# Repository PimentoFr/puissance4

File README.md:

# puissance4
Il s'agit d'un puissance 4 lumineux connecté et interractif par le chat Twitch

# Description

Ce projet a pour but de réaliser un écran LED basé sur des WS2812B (led addressable individuellement), piloté par un raspberry pi
afin d'ouvrir une surface de jeu pour le puissance 4. Le jeu sera connecté et intéractif avec le chat Twitch pour permettre
aux viewers et participants de chat de jouer leur partie.

Dans ce projet, l'arborescence est la suivante:
- `hardware` : L'ensemble des documents permettant la réalisation des cartes électroniques du projet
    - `panneau_led`: Contient le design de la carte électronique des dalles de LEDs.
    - `mainboard`: Carte principale permettant l'alimentation des Bucks 24V-5V pour les colonnes de la matrice de LEDs et la connection
    du Raspberry Pi.
- `software` : Bientôt.

# Logiciels

Les logiciels utilisées sont les suivants:
- hardware : [Kicad](https://kicad.org/download/)

# Electronique

## Panneau led

Les panneaux LEDs sont des panneaux de 90x90mm qui accueille chacun 9 LEDs de type WS2812B.
Elles sont tous chaînés de la manière suivante:

```
1 -> 2 -> 3
 <--------|
4 -> 5 -> 6
 <--------|
7 -> 8 -> 9
```

## Mainboard

Cette carte permet d'accueillir la source d'alimentation (Prise Power Jack 24V 4A) et de la répartir sur 7 borniers afin d'y brancher 7 convertisseurs DC/DC Buck pour alimenter chacun des 7 colonnes de la matrice de LEDs.
A cela, un support femelle 2x20 pins permet de connnecter un
Raspberry Pi afin d'assurer l'intelligence et le pilotage de ce
panneau LEDs. Un level shifter 3.3V->5V permet d'assurer l'adaptation de niveau logique entre la commande émise par le
Raspberry Pi et les WS2812B.

Plusieurs connecteurs supplémentaires permettent de brancher
d'autres périphériques au besoin en I2C/SPI/UART.

# Licence

Le projet est open-source. Tout le monde peut l'utiliser en laissant la référence à son auteur.

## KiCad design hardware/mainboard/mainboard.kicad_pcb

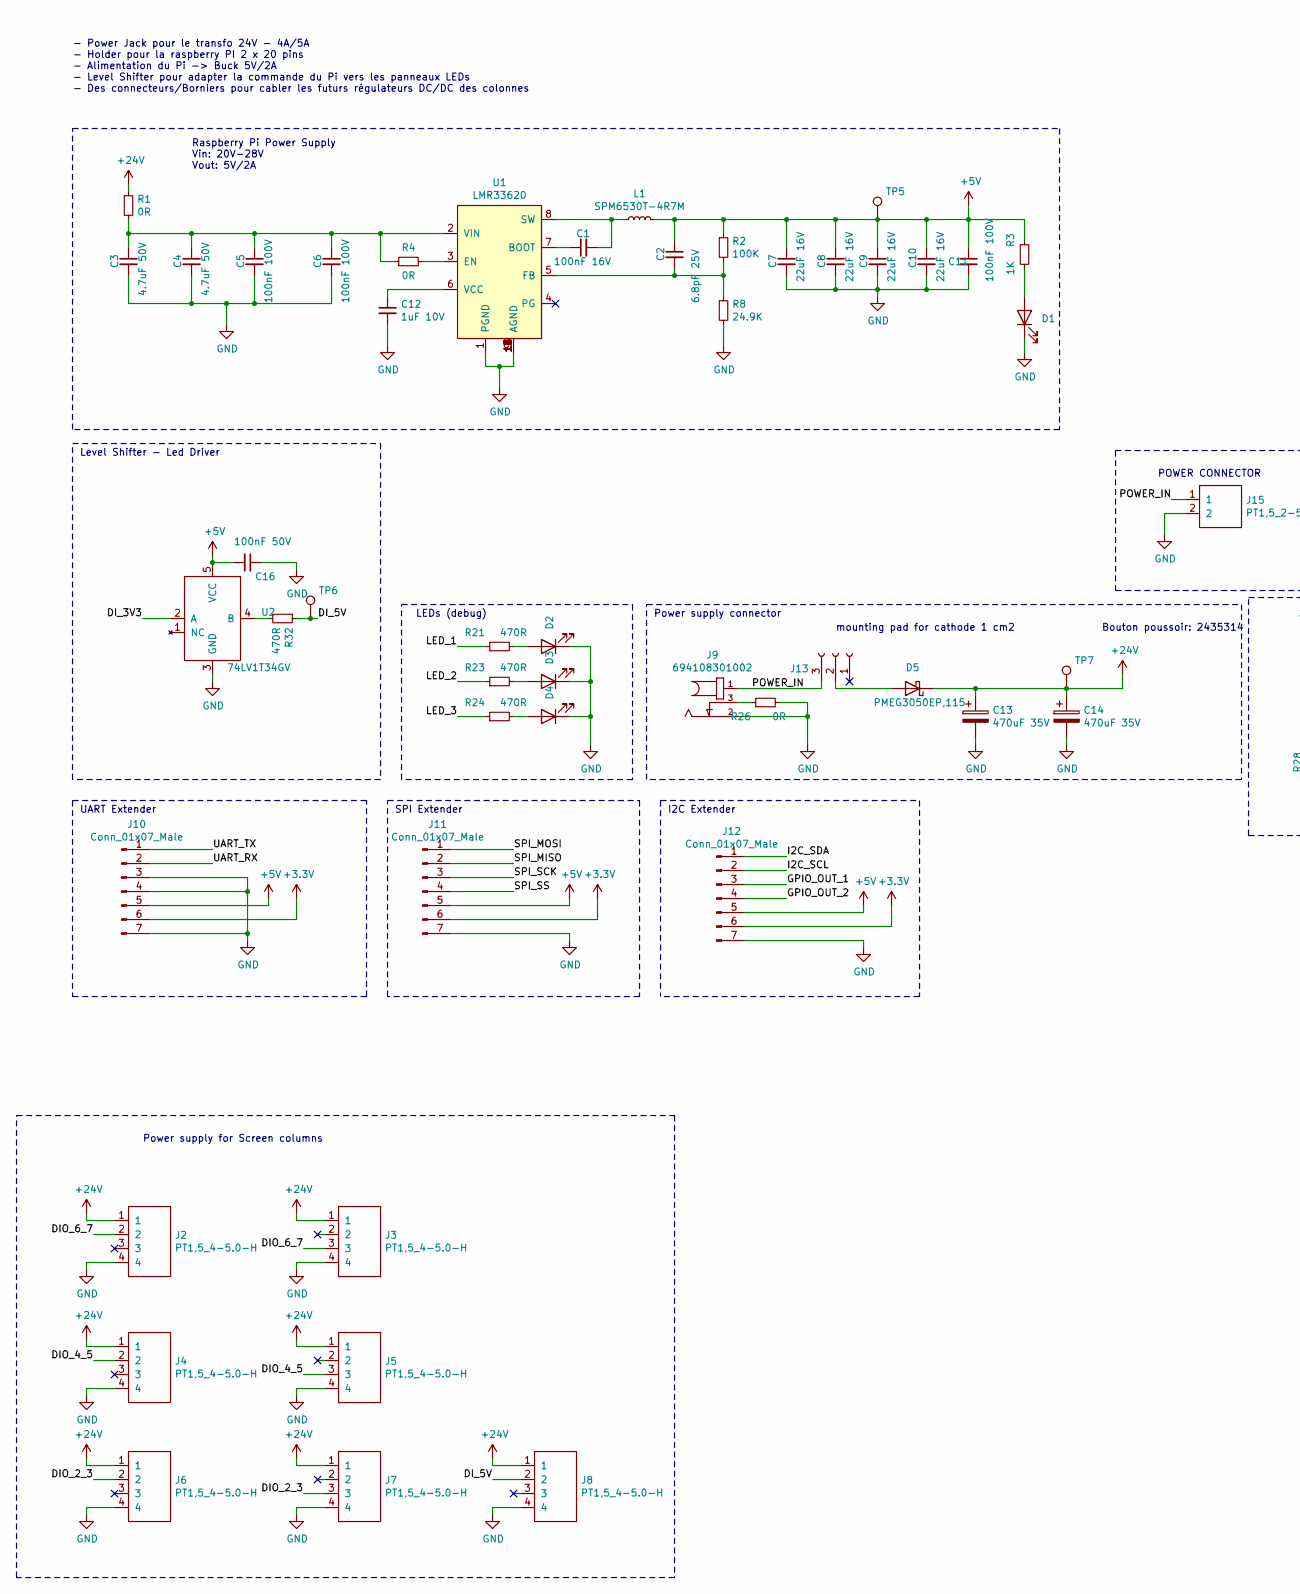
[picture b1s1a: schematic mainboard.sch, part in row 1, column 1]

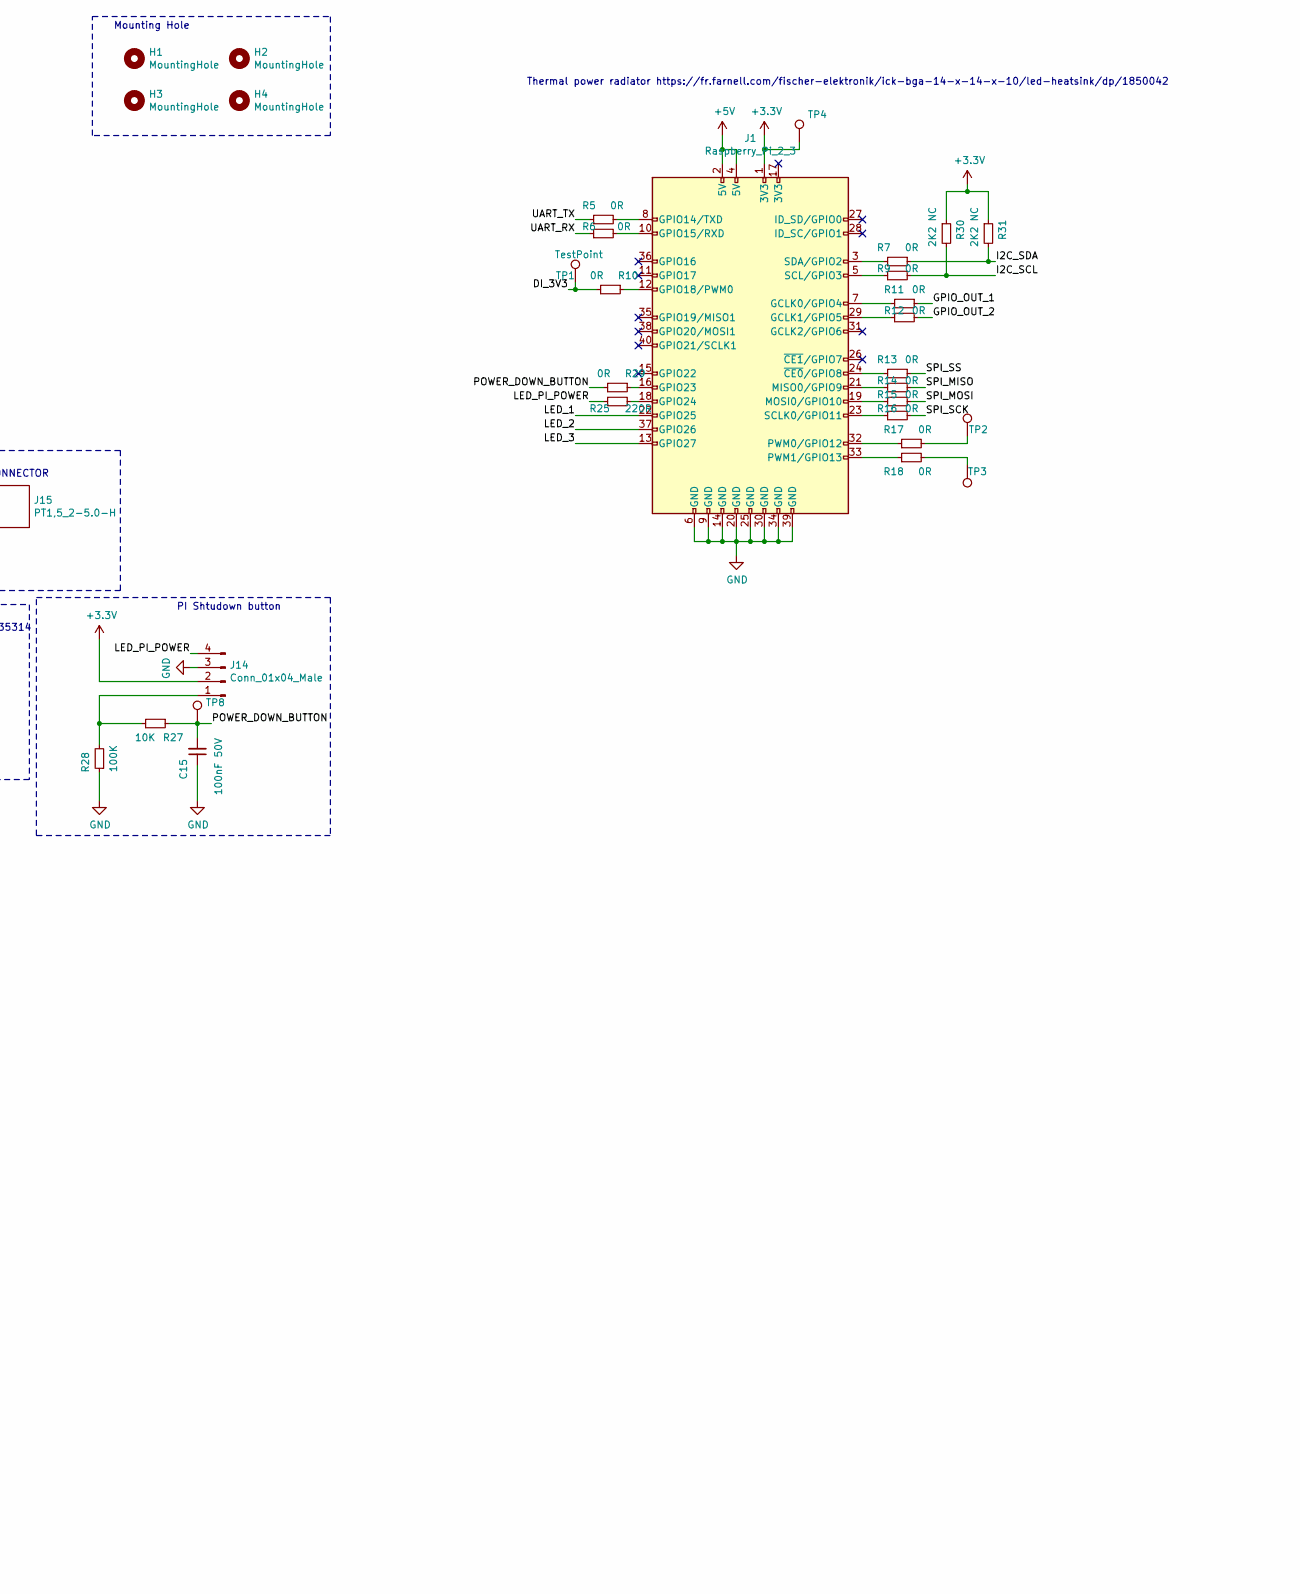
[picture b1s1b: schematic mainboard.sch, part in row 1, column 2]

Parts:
C1: 100nF 16V; C_0402_1005Metric; farnell 2627345
C2: 6.8pF 25V; C_0402_1005Metric; farnell 2781440
C3: 4.7uF 50V; C_1206_3216Metric_Pad1.42x1.75mm_HandSolder; farnell 1735545
C4: 4.7uF 50V; C_1206_3216Metric_Pad1.42x1.75mm_HandSolder
C5, C6, C11: 100nF 100V; C_0603_1608Metric_Pad1.05x0.95mm_HandSolder; farnell 1828921
C7, C8, C9, C10: 22uF 16V; C_1210_3225Metric_Pad1.42x2.65mm_HandSolder; farnell 2112725
C12: 1uF 10V; C_0603_1608Metric_Pad1.05x0.95mm_HandSolder; farnell 9227776
C13, C14: 470uF 35V; CP_Radial_D10.0mm_P5.00mm; farnell 2805546
C15, C16: 100nF 50V; C_0402_1005Metric
D1, D2, D3, D4: MCL-S250GC; LED_1206_3216Metric_Pad1.42x1.75mm_HandSolder; farnell 1581232
D5: PMEG3050EP,115; D_SOD-128; farnell 1829197
H1, H2, H3, H4: MountingHole; MountingHole_2.5mm
J1: Raspberry_Pi_2_3; MODULE_RASPBERRY_PI_3_MODEL_B+_REVERSE
J2, J3, J4, J5, J6, J7, J8: PT1,5_4-5.0-H; PT1,5-4-5.0-H; farnell 1793677
J9: 694108301002; PART-NUMBER 694108301002; farnell 2472153
J10, J11: Conn_01x07_Male; PinHeader_1x07_P2.54mm_Vertical
J12: Conn_01x07_Male; PinHeader_1x07_P2.54mm_Vertical; farnell 2847167
J13: Conn_01x03_Female; TerminalBlock_bornier-3_P5.08mm
J14: Conn_01x04_Male; PinSocket_1x04_P2.54mm_Vertical
J15: PT1,5_2-5.0-H; PT1,5-2-5.0-H
L1: SPM6530T-4R7M; SPM6530T; farnell 2215613
R1: 0R; R_0805_2012Metric_Pad1.15x1.40mm_HandSolder
R2, R28: 100K; R_0402_1005Metric
R3: 1K; R_0402_1005Metric
R4, R5, R6, R7, R9, R10, R11, R12, R13, R14, R15, R16, R17, R18, R29: 0R; R_0402_1005Metric
R8: 24.9K; R_0402_1005Metric
R21, R23, R24, R32: 470R; R_0402_1005Metric
R25: 220R; R_0402_1005Metric
R26: 0R; R_1206_3216Metric
R27: 10K; R_0402_1005Metric
R30, R31: 2K2 NC; R_0402_1005Metric
TP1, TP2, TP3, TP4, TP5, TP6, TP7, TP8: TestPoint; TestPoint_Pad_D1.0mm
U1: LMR33620; 8pin-HSOIC; farnell 3007264
U2: 74LV1T34GV; SOT-753; farnell 3485601

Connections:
+3V3: J1.1 (3V3), J10.6, J11.6, J12.6, J14.2, R30.1, R31.1, TP4.1
+5V: C2.1, C7.1, C8.1, C9.1, C10.1, C11.1, C16.2, J1.2 (5V), J1.4 (5V), J10.5, J11.5, J12.5, L1.2, R2.1, R3.1, TP5.1, U2.5 (VCC)
+24V: C13.1, C14.1, D5.1 (K), J2.1, J3.1, J4.1, J5.1, J6.1, J7.1, J8.1, R1.1, TP7.1
/DIO_2_3: J6.2, J7.3
/DIO_4_5: J4.2, J5.3
/DIO_6_7: J2.2, J3.3
/DI_3V3: R10.2, TP1.1, U2.2 (A)
/DI_5V: J8.2, R32.1, TP6.1
/GPIO_OUT_1: J12.3, R11.1
/GPIO_OUT_2: J12.4, R12.1
/I2C_SCL: J12.2, R9.1, R30.2
/I2C_SDA: J12.1, R7.1, R31.2
/LED_1: J1.22 (GPIO25), R21.1
/LED_2: J1.37 (GPIO26), R23.1
/LED_3: J1.13 (GPIO27), R24.1
/LED_PI_POWER: J14.4, R25.1
/POWER_DOWN_BUTTON: C15.2, R27.1, R29.2, TP8.1
/POWER_IN: J9.1, J13.3, J15.1
/SPI_MISO: J11.2, R14.1
/SPI_MOSI: J11.1, R15.1
/SPI_SCK: J11.3, R16.1
/SPI_SS: J11.4, R13.1
/UART_RX: J10.2, R6.1
/UART_TX: J10.1, R5.1
GND: C3.2, C4.2, C5.2, C6.2, C7.2, C8.2, C9.2, C10.2, C11.2, C12.2, C13.2, C14.2, C15.1, C16.1, D1.1 (K), D2.1 (K), D3.1 (K), D4.1 (K), J1.6 (GND), J1.9 (GND), J1.14 (GND), J1.20 (GND), J1.25 (GND), J1.30 (GND), J1.34 (GND), J1.39 (GND), J2.4, J3.4, J4.4, J5.4, J6.4, J7.4, J8.4, J9.2, J10.3, J10.4, J10.7, J11.7, J12.7, J14.3, J15.2, R8.2, R26.2, R28.1, U1.1 (PGND), U1.9 (AGND), U1.10 (AGND), U1.11 (AGND), U1.12 (AGND), U1.13 (AGND), U1.14 (AGND), U1.15 (AGND), U1.16 (AGND), U1.17 (AGND), U2.3 (GND)
unnamed: C1.1, U1.7 (BOOT)
unnamed: C1.2, L1.1, U1.8 (SW)
unnamed: C2.2, R2.2, R8.1, U1.5 (FB)
unnamed: C3.1, C4.1, C5.1, C6.1, R1.2, R4.1, U1.2 (VIN)
unnamed: C12.1, U1.6 (VCC)
unnamed: D1.2 (A), R3.2
unnamed: D2.2 (A), R21.2
unnamed: D3.2 (A), R23.2
unnamed: D4.2 (A), R24.2
unnamed: D5.2 (A), J13.2
unnamed: J1.3 (SDA/GPIO2), R7.2
unnamed: J1.5 (SCL/GPIO3), R9.2
unnamed: J1.7 (GCLK0/GPIO4), R11.2
unnamed: J1.8 (GPIO14/TXD), R5.2
unnamed: J1.10 (GPIO15/RXD), R6.2
unnamed: J1.12 (GPIO18/PWM0), R10.1
unnamed: J1.16 (GPIO23), R29.1
unnamed: J1.18 (GPIO24), R25.2
unnamed: J1.19 (MOSI0/GPIO10), R15.2
unnamed: J1.21 (MISO0/GPIO9), R14.2
unnamed: J1.23 (SCLK0/GPIO11), R16.2
unnamed: J1.24 (~CE0~/GPIO8), R13.2
unnamed: J1.29 (GCLK1/GPIO5), R12.2
unnamed: J1.32 (PWM0/GPIO12), R17.1
unnamed: J1.33 (PWM1/GPIO13), R18.1
unnamed: J9.3, R26.1
unnamed: J14.1, R27.2, R28.2
unnamed: R4.2, U1.3 (EN)
unnamed: R17.2, TP2.1
unnamed: R18.2, TP3.1
unnamed: R32.2, U2.4 (B)

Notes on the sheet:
- Power Jack pour le transfo 24V - 4A/5A - Holder pour la raspberry PI 2 x 20 pins - Alimentation du Pi -> Buck 5V/2A - Level Shifter pour adapter la commande du Pi vers les panneaux LEDs - Des connecteurs/Borniers pour cabler les futurs régulateurs DC/DC des colonnes
Raspberry Pi Power Supply Vin: 20V-28V Vout: 5V/2A
Power supply connector
Level Shifter - Led Driver
Power supply for Screen columns
LEDs (debug)
UART Extender
SPI Extender
I2C Extender
mounting pad for cathode 1 cm2
Bouton poussoir: 2435314
POWER CONNECTOR
PI Shtudown button
Mounting Hole
Thermal power radiator https://fr.farnell.com/fischer-elektronik/ick-bga-14-x-14-x-10/led-heatsink/dp/1850042

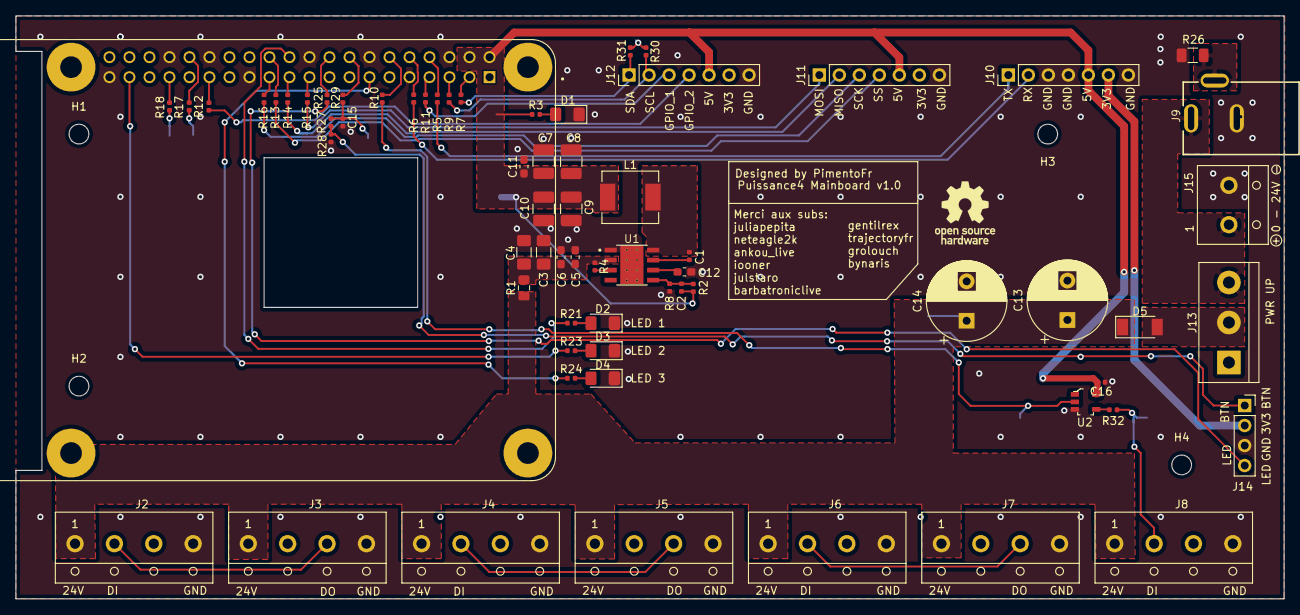
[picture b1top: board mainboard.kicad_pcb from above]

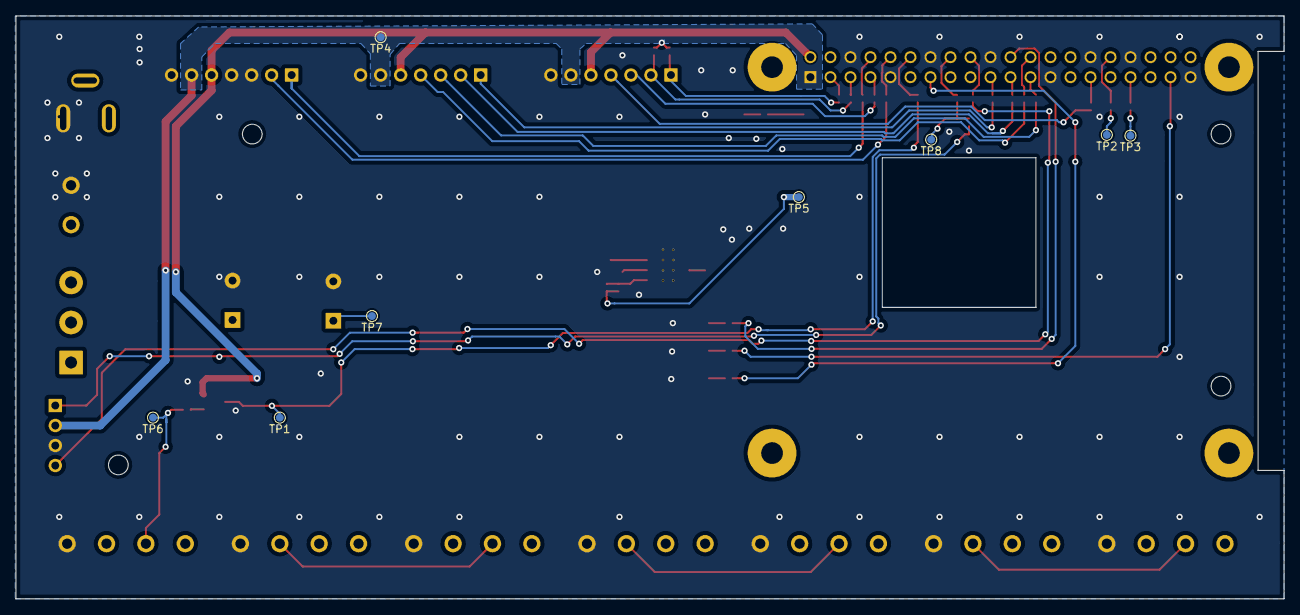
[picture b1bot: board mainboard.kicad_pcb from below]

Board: 2 copper layers, 161.0 x 74.0 mm, 80 parts (8 on the bottom side), 56 nets.

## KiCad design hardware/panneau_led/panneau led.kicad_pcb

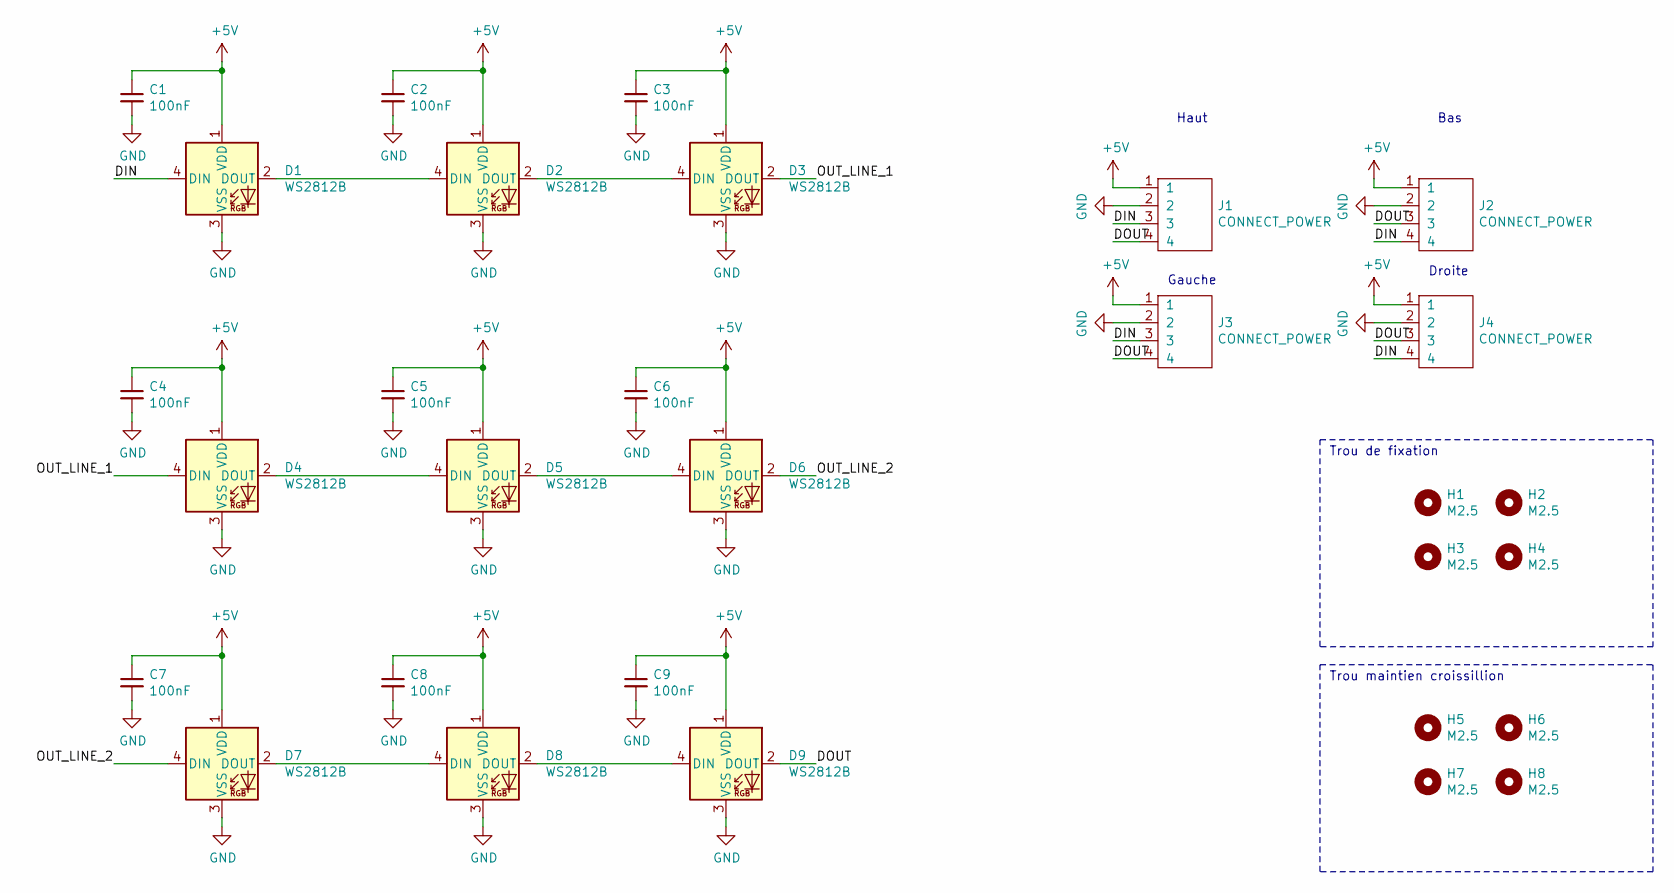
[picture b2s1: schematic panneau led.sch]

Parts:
C1, C2, C3, C4, C5, C6, C7, C8, C9: 100nF; C_0402_1005Metric; lcsc C1525
D1, D2, D3, D4, D5, D6, D7, D8, D9: WS2812B; LED_WS2812B_PLCC4_5.0x5.0mm_P3.2mm; lcsc C114586
H1, H2, H3, H4, H5, H6, H7, H8: M2.5; MountingHole_2.7mm_M2.5; lcsc NA
J1, J2, J3, J4: CONNECT_POWER; lcsc NA

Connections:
+5V: C1.1, C2.1, C3.1, C4.1, C5.1, C6.1, C7.1, C8.1, C9.1, D1.1 (VDD), D2.1 (VDD), D3.1 (VDD), D4.1 (VDD), D5.1 (VDD), D6.1 (VDD), D7.1 (VDD), D8.1 (VDD), D9.1 (VDD), J1.1, J2.1, J3.1, J4.1
/DIN: D1.4 (DIN), J1.3, J2.4, J3.3, J4.4
/DOUT: D9.2 (DOUT), J1.4, J2.3, J3.4, J4.3
/OUT_LINE_1: D3.2 (DOUT), D4.4 (DIN)
/OUT_LINE_2: D6.2 (DOUT), D7.4 (DIN)
GND: C1.2, C2.2, C3.2, C4.2, C5.2, C6.2, C7.2, C8.2, C9.2, D1.3 (VSS), D2.3 (VSS), D3.3 (VSS), D4.3 (VSS), D5.3 (VSS), D6.3 (VSS), D7.3 (VSS), D8.3 (VSS), D9.3 (VSS), J1.2, J2.2, J3.2, J4.2
unnamed: D1.2 (DOUT), D2.4 (DIN)
unnamed: D2.2 (DOUT), D3.4 (DIN)
unnamed: D4.2 (DOUT), D5.4 (DIN)
unnamed: D5.2 (DOUT), D6.4 (DIN)
unnamed: D7.2 (DOUT), D8.4 (DIN)
unnamed: D8.2 (DOUT), D9.4 (DIN)

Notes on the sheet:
Haut
Bas
Gauche
Droite
Trou de fixation
Trou maintien croissillion

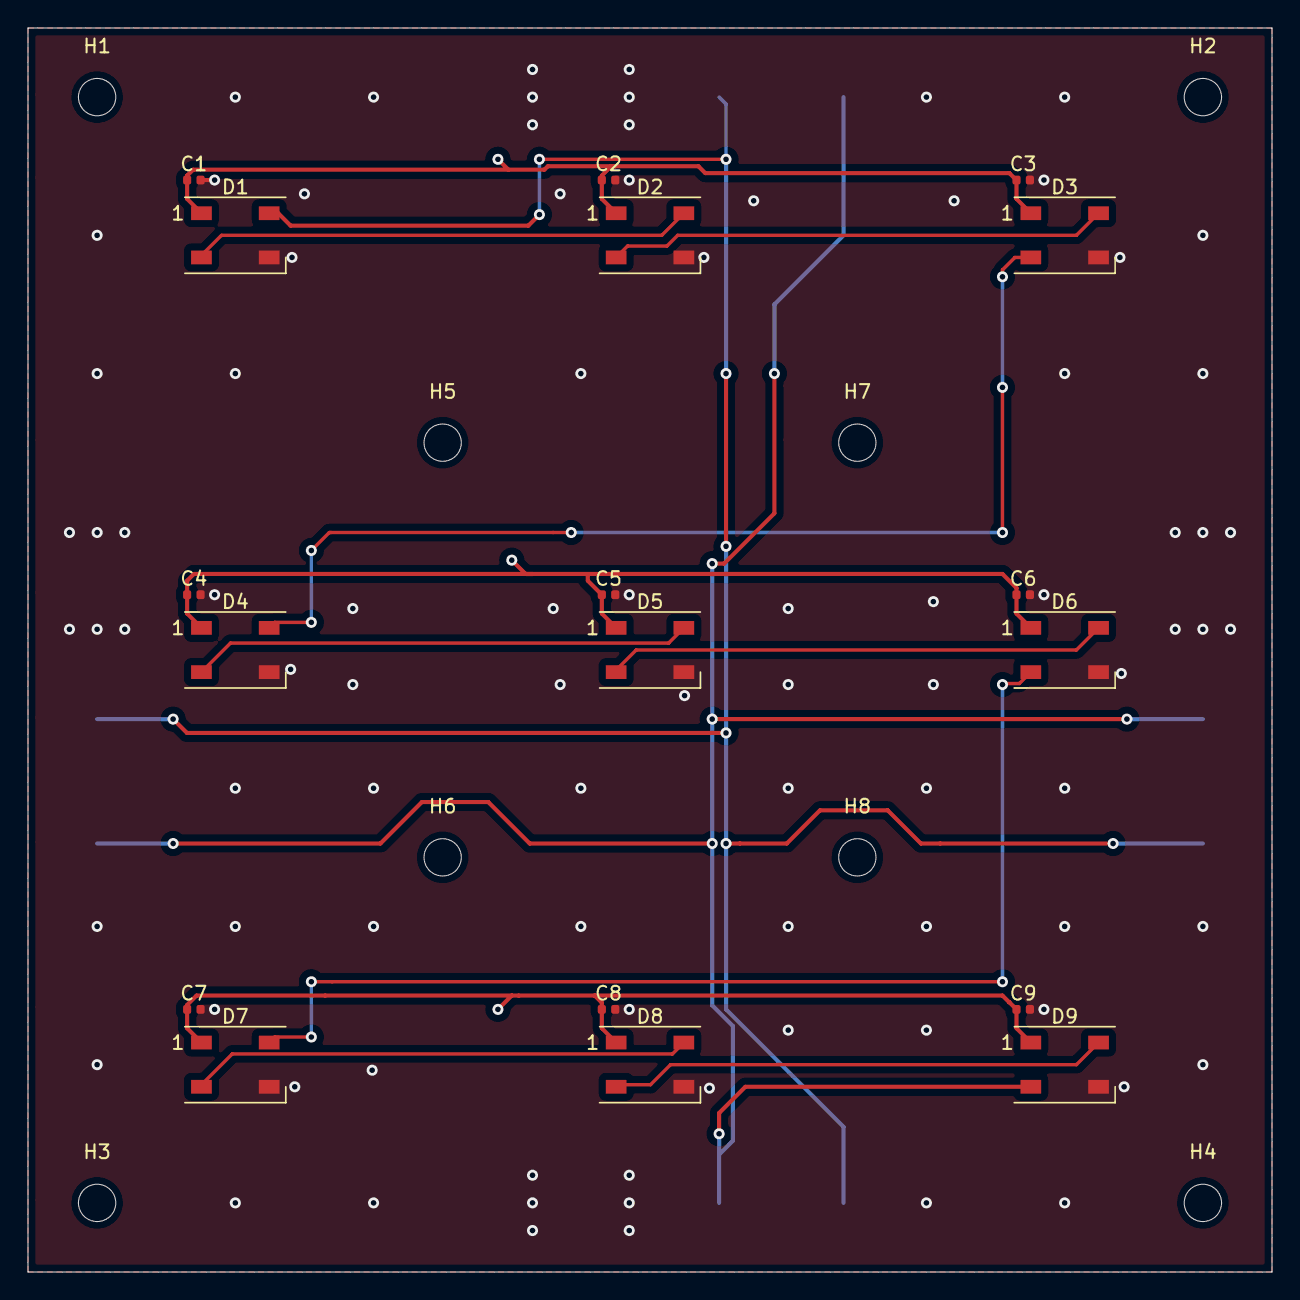
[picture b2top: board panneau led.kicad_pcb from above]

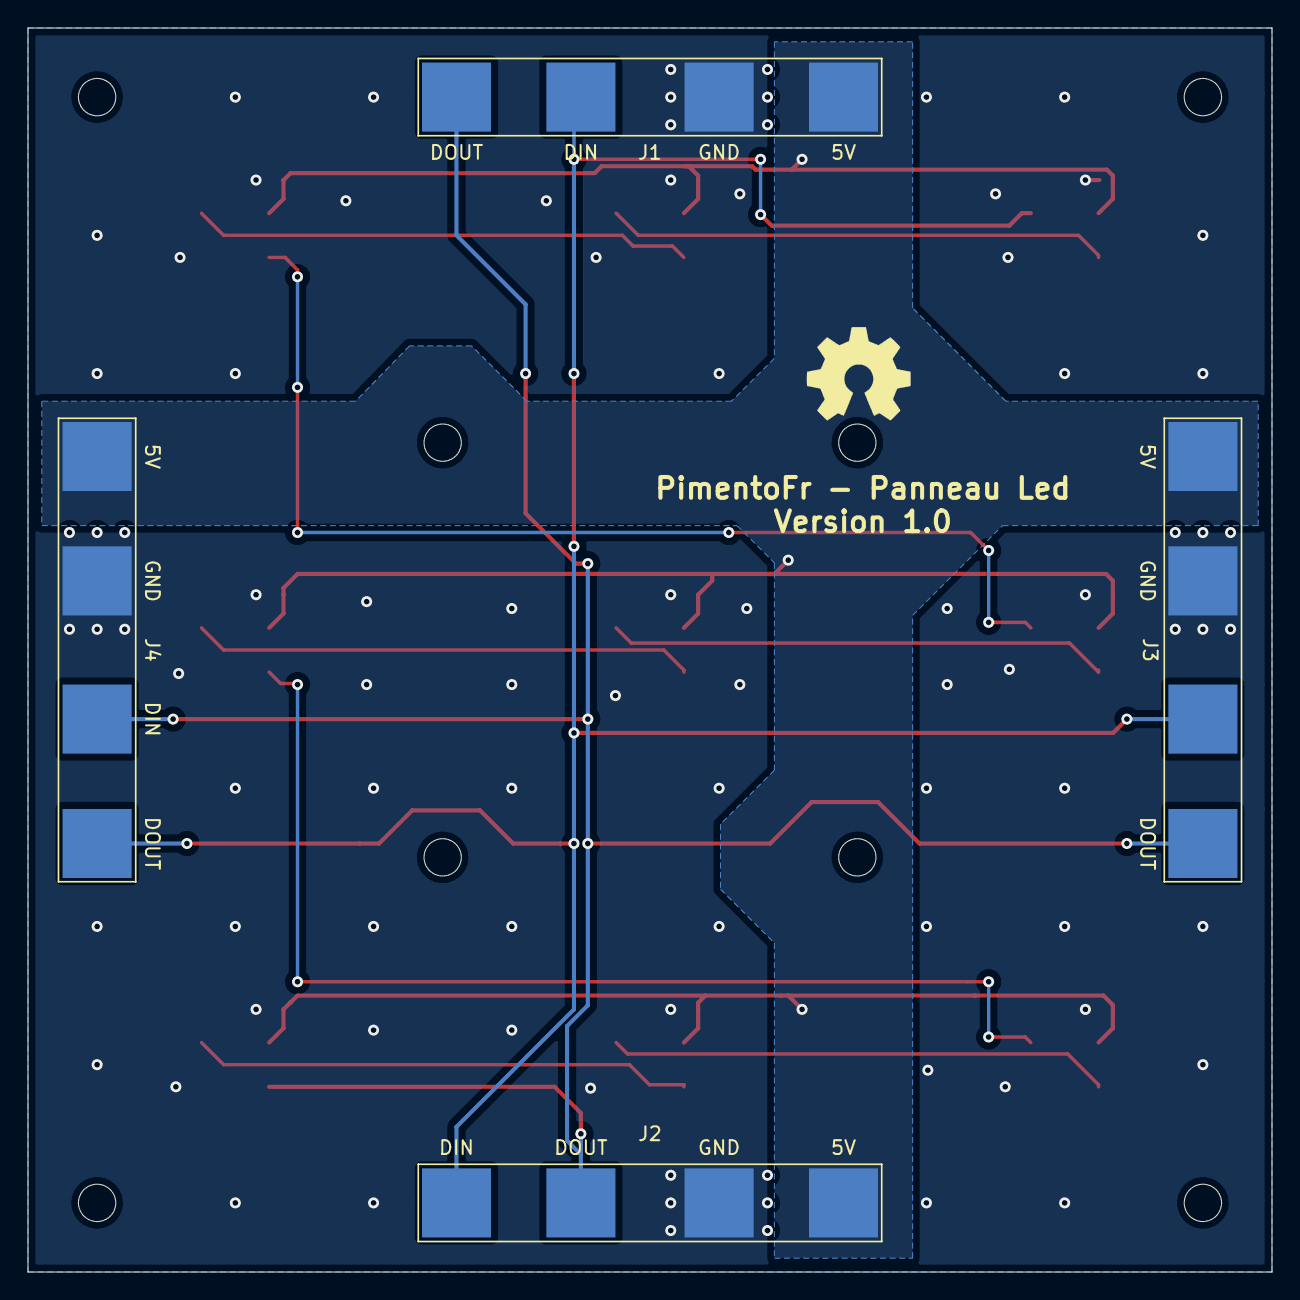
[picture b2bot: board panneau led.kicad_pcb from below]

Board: 2 copper layers, 90.0 x 90.0 mm, 30 parts (4 on the bottom side), 12 nets.

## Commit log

2021-02-05 feat: hw: add design files for the led board
2021-02-05 doc: complete readme for the led panel board
2021-02-05 feat: hw: add design files for mainboard
    This board permit to control a matrix of 7x7 LED panels. This board should be powered up by a 24V 4A power supply.
    A 2x20 pins connectors can host a Raspberry Pi.
2021-02-08 wip: feat: meca: add separator for led panels
    This element is designed with FreeCad
2021-02-13 wip: start setup project with first screen mapping
2021-02-13 wip: trials simulator
2021-02-18 wip font
2021-02-20 wip: soft: add display engine and text/text scroll widgets
2021-02-20 wip: soft: add rect fill widget
2021-02-20 wip: soft: add vertical or horizontal line widget
2021-02-20 fix text scroll
2021-02-20 wip: soft: add disc widget
2021-02-20 refactor: soft: create a new file hosting Direction class
2021-02-20 wip: sw: feat: Implement simulator throught Websocket
    A websocket server is run if a stub is set on the display initialization.
    The websocket server address is localhost:6789
    The simulator is available at software/socket/index.html
